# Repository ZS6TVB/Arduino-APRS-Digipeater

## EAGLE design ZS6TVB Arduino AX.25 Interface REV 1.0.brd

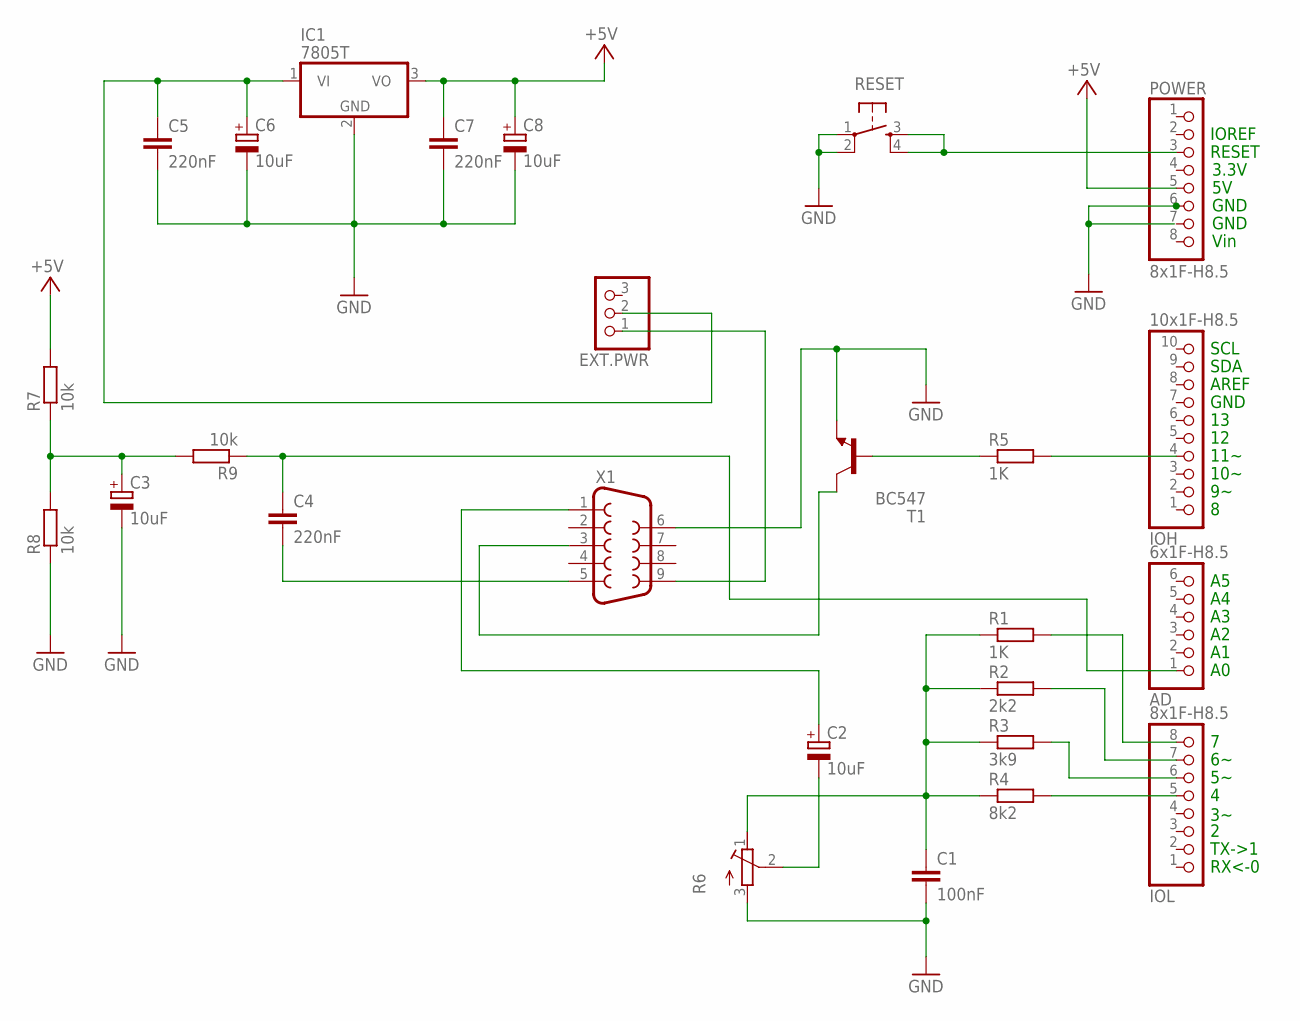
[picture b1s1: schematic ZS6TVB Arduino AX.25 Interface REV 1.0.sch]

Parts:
AD: 6x1F-H8.5; 1X06
C1: 100nF; C050-024X044
C2, C3, C6, C8: 10uF; E5-10,5
C4, C5, C7: 220nF; C050-024X044
EXT.PWR: PINHD-1X3; 1X03
IC1: 7805T; TO220H
IOH: 10x1F-H8.5; 1X10
IOL: 8x1F-H8.5; 1X08
POWER: 8x1F-H8.5; 1X08
R1, R5: 1K; 0207/7
R2: 2k2; 0207/7
R3: 3k9; 0207/7
R4: 8k2; 0207/7
R6: R-TRIMMT93XB; RTRIMT93XB
R7, R8, R9: 10k; 0207/7
RESET: TAC_SWITCHPTH; TACTILE-PTH
T1: BC547; TO92
X1: F09HP

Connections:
+5V: C7.1, C8.+, IC1.3 (VO), POWER.5, R7.2
GND: C1.2, C3.-, C5.2, C6.-, C7.2, C8.-, IC1.2 (GND), POWER.6, R6.3 (A), R8.1, RESET.1, RESET.2, T1.1 (E), X1.6
unnamed: POWER.3, RESET.3, RESET.4
unnamed: IOL.8, R1.2
unnamed: IOL.7, R2.2
unnamed: IOL.5, R4.2
unnamed: EXT.PWR.1, X1.9
unnamed: C2.+, X1.1
unnamed: IOL.6, R3.2
unnamed: C1.1, R1.1, R2.1, R3.1, R4.1, R6.1 (E)
unnamed: C2.-, R6.2 (S)
unnamed: IOH.4, R5.2
unnamed: R5.1, T1.2 (B)
unnamed: T1.3 (C), X1.3
unnamed: C4.2, X1.5
unnamed: C3.+, R7.1, R8.2, R9.2
unnamed: AD.1, C4.1, R9.1
unnamed: C5.1, C6.+, EXT.PWR.2, IC1.1 (VI)

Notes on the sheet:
RX<-0
TX->1
10~
11~
SDA
SCL
GND
3.3V
RESET
IOREF
Vin
AREF

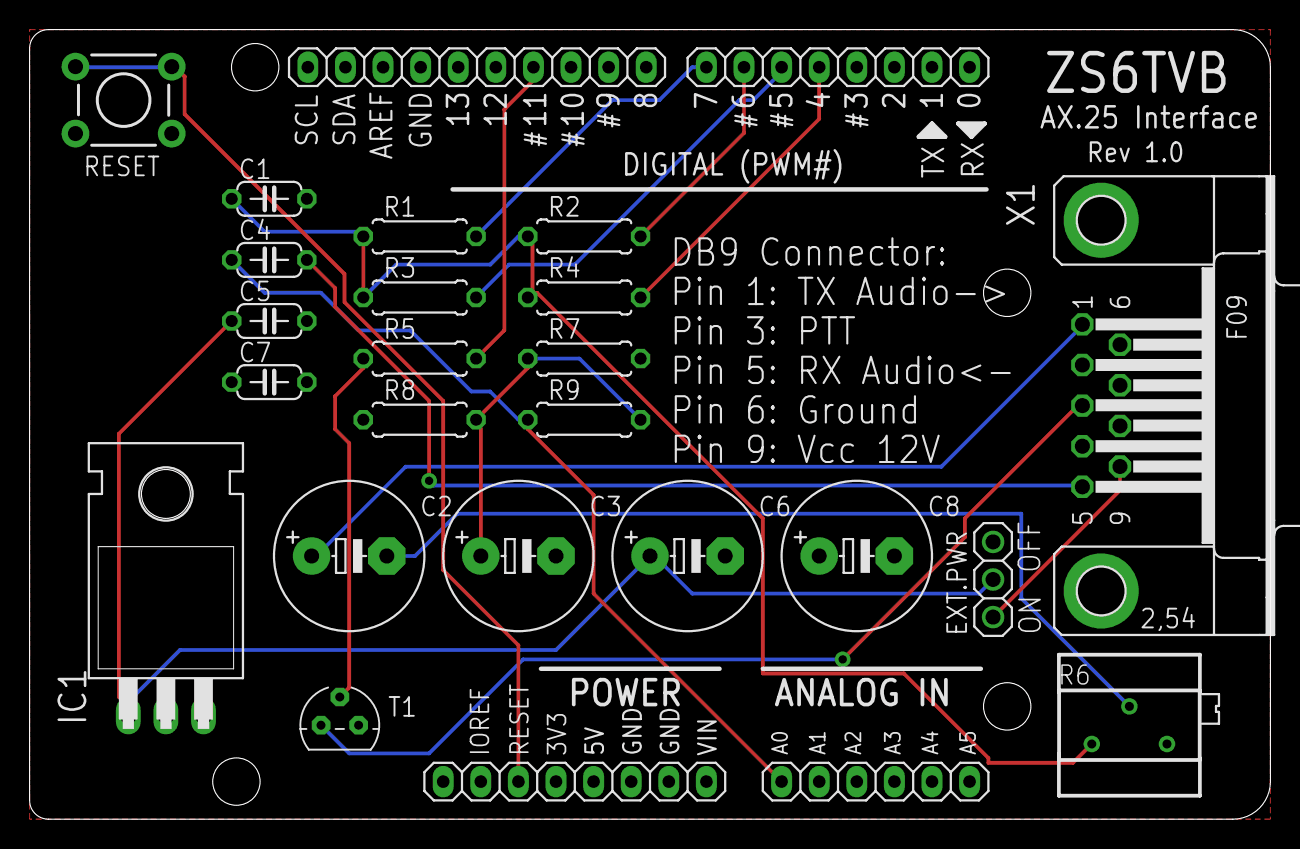
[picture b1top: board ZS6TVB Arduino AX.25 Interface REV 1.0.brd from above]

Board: 2 copper layers, 83.8 x 53.3 mm, 26 parts (0 on the bottom side), 18 nets.

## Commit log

2014-06-05 First Checkin

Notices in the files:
parts and their libraries:
SparkFun-Electromechanical: Licensing: Creative Commons ShareAlike 4.0 International - https://creativecommons.org/licenses/by-sa/4.0
